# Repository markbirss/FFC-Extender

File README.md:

# FFC-Extender and Adapter
FFC (Flexible Flat Cable) Extender and Adapter.

* Open-Source and released under the [Creative Commons Attribution Share-Alike License](https://creativecommons.org/licenses/by-sa/4.0/).
* **[Documentation on learn.watterott.com](https://learn.watterott.com)**

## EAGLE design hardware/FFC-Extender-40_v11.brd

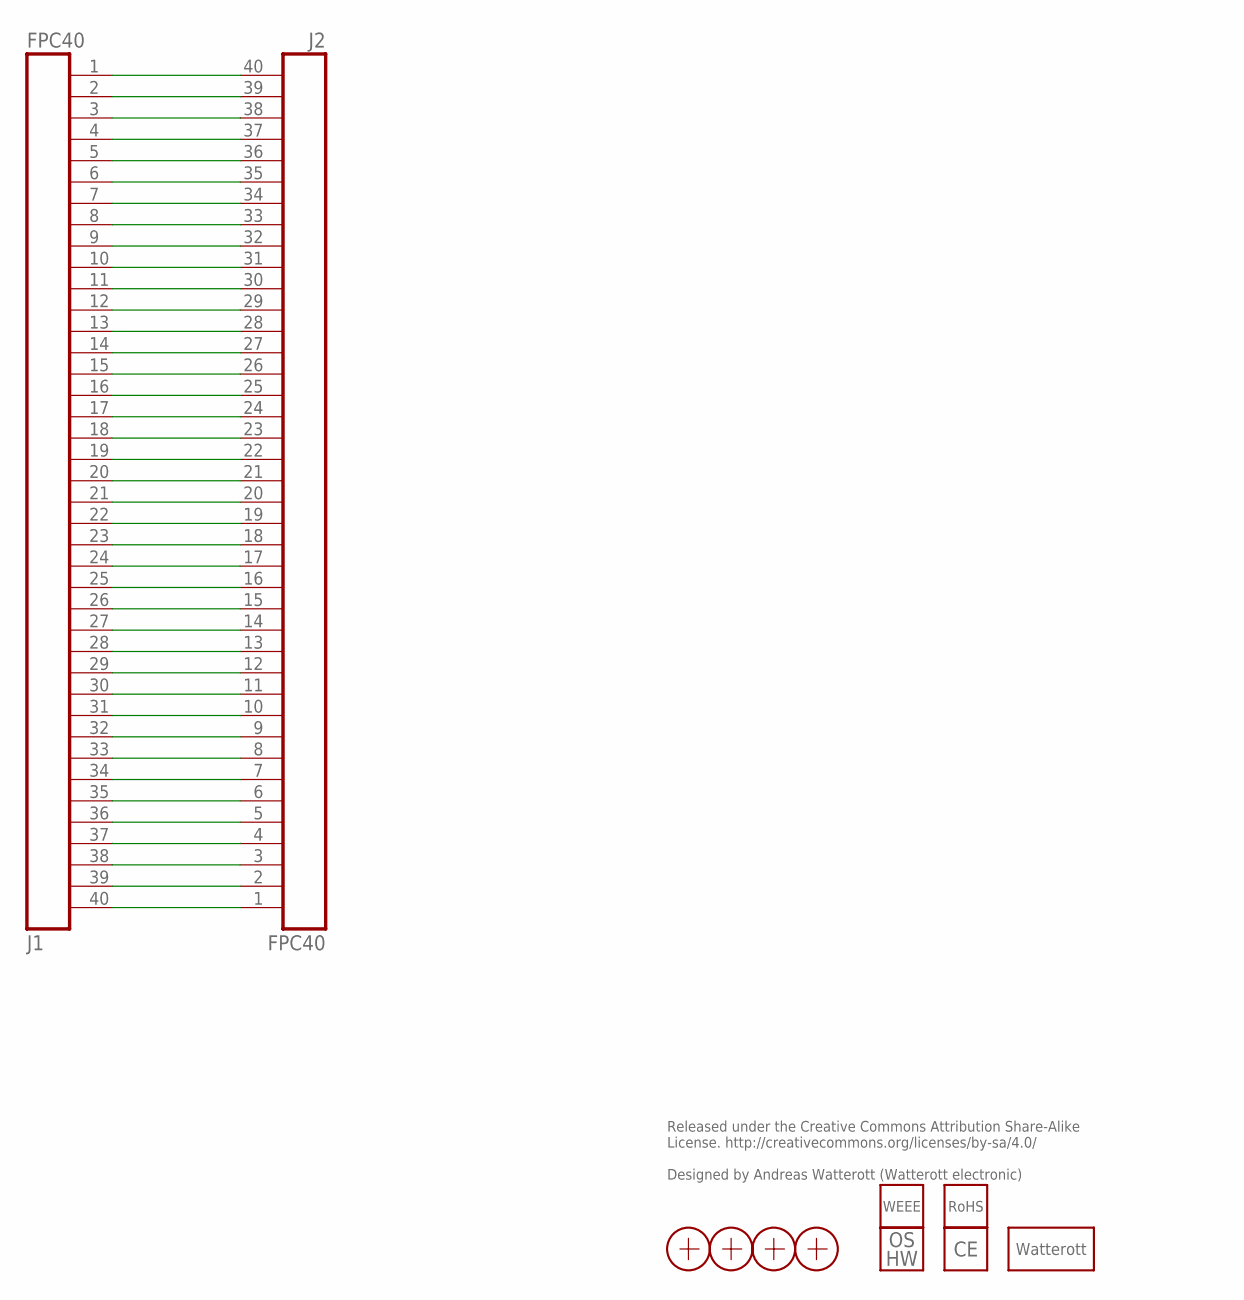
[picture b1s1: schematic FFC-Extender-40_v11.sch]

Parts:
J1, J2: FPC40; FPC40-0.5
LOGO1: LOGO_SPARK-2; SPARK_2MM
LOGO2: LOGO_CE-2; CE_2MM
LOGO3: LOGO_OSHW-2; OSHW_2MM
LOGO4: LOGO_ROHS-2; ROHS_2MM
LOGO5: LOGO_WEEE-4; WEEE_4MM
X1, X2, X3, X4: PASSER

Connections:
unnamed: J1.1, J2.40
unnamed: J1.2, J2.39
unnamed: J1.3, J2.38
unnamed: J1.4, J2.37
unnamed: J1.5, J2.36
unnamed: J1.6, J2.35
unnamed: J1.7, J2.34
unnamed: J1.8, J2.33
unnamed: J1.9, J2.32
unnamed: J1.10, J2.31
unnamed: J1.11, J2.30
unnamed: J1.12, J2.29
unnamed: J1.13, J2.28
unnamed: J1.14, J2.27
unnamed: J1.15, J2.26
unnamed: J1.16, J2.25
unnamed: J1.17, J2.24
unnamed: J1.18, J2.23
unnamed: J1.19, J2.22
unnamed: J1.20, J2.21
unnamed: J1.21, J2.20
unnamed: J1.22, J2.19
unnamed: J1.23, J2.18
unnamed: J1.24, J2.17
unnamed: J1.25, J2.16
unnamed: J1.26, J2.15
unnamed: J1.27, J2.14
unnamed: J1.28, J2.13
unnamed: J1.29, J2.12
unnamed: J1.30, J2.11
unnamed: J1.31, J2.10
unnamed: J1.32, J2.9
unnamed: J1.33, J2.8
unnamed: J1.34, J2.7
unnamed: J1.35, J2.6
unnamed: J1.36, J2.5
unnamed: J1.37, J2.4
unnamed: J1.38, J2.3
unnamed: J1.39, J2.2
unnamed: J1.40, J2.1

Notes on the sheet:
Released under the Creative Commons Attribution Share-Alike License. http://creativecommons.org/licenses/by-sa/4.0/ Designed by Andreas Watterott (Watterott electronic)

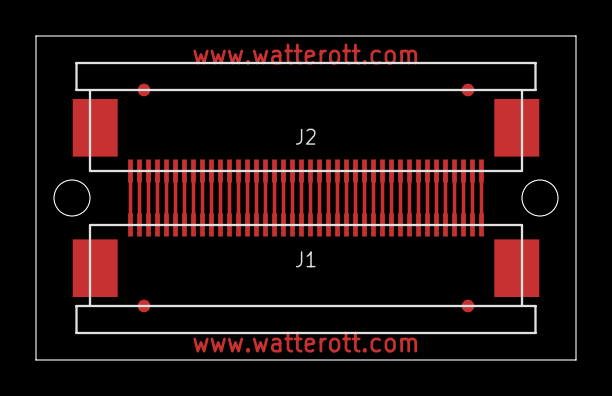
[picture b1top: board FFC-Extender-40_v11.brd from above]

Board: 2 copper layers, 30.0 x 18.0 mm, 11 parts (5 on the bottom side), 40 nets.

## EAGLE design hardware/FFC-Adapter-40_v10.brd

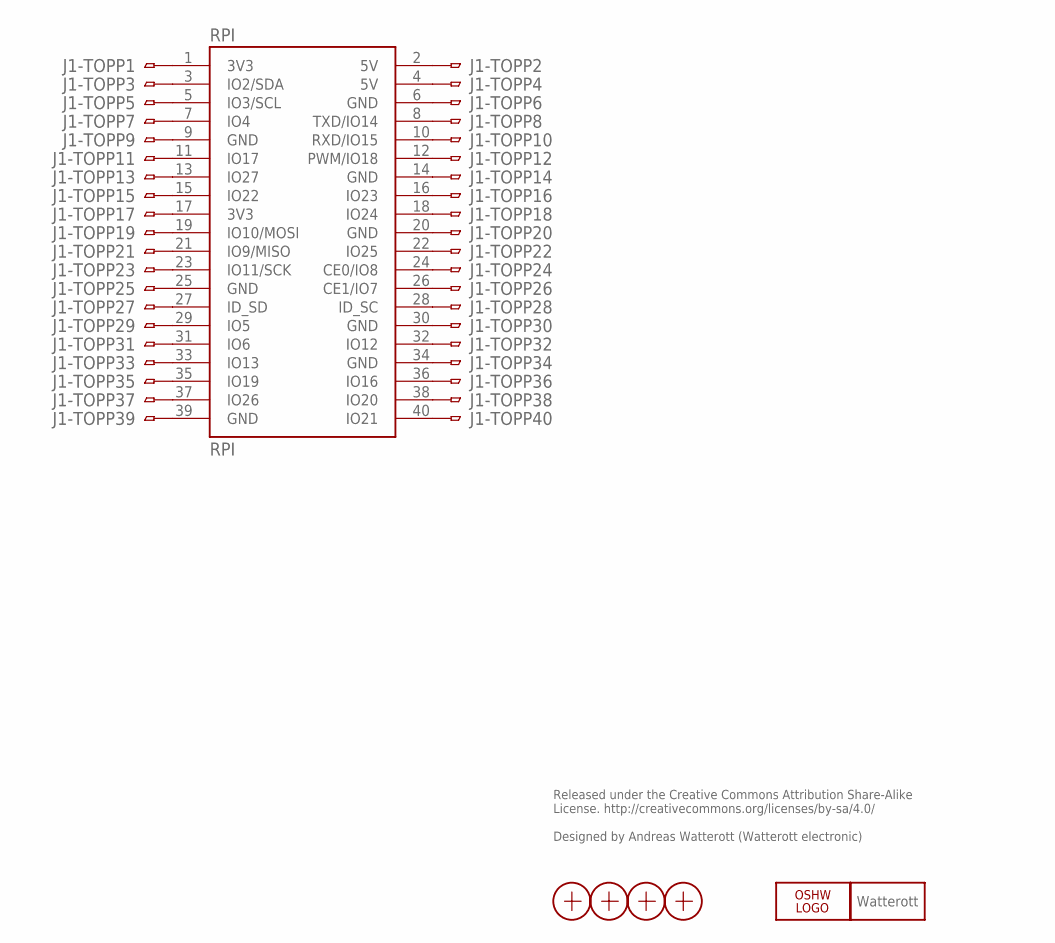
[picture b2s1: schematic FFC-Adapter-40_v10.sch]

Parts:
J1-TOP: FPC40_PIN; FPC40-0.5
LOGO1: OSHW_LOGO_6MILX0150-NT; OSHW_6X150_NOTEXT
LOGO3: LOGO_SPARK-4; SPARK_4MM
RPI: RPI; RPI-B+_CON
X1, X2, X3, X4: PASSER

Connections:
unnamed: J1-TOP.40, RPI.40 (IO21)
unnamed: J1-TOP.2, RPI.2 (5V)
unnamed: J1-TOP.3, RPI.3 (IO2/SDA)
unnamed: J1-TOP.4, RPI.4 (5V)
unnamed: J1-TOP.6, RPI.6 (GND)
unnamed: J1-TOP.5, RPI.5 (IO3/SCL)
unnamed: J1-TOP.7, RPI.7 (IO4)
unnamed: J1-TOP.8, RPI.8 (TXD/IO14)
unnamed: J1-TOP.9, RPI.9 (GND)
unnamed: J1-TOP.10, RPI.10 (RXD/IO15)
unnamed: J1-TOP.11, RPI.11 (IO17)
unnamed: J1-TOP.12, RPI.12 (PWM/IO18)
unnamed: J1-TOP.13, RPI.13 (IO27)
unnamed: J1-TOP.14, RPI.14 (GND)
unnamed: J1-TOP.15, RPI.15 (IO22)
unnamed: J1-TOP.16, RPI.16 (IO23)
unnamed: J1-TOP.17, RPI.17 (3V3)
unnamed: J1-TOP.18, RPI.18 (IO24)
unnamed: J1-TOP.19, RPI.19 (IO10/MOSI)
unnamed: J1-TOP.20, RPI.20 (GND)
unnamed: J1-TOP.21, RPI.21 (IO9/MISO)
unnamed: J1-TOP.22, RPI.22 (IO25)
unnamed: J1-TOP.23, RPI.23 (IO11/SCK)
unnamed: J1-TOP.24, RPI.24 (CE0/IO8)
unnamed: J1-TOP.25, RPI.25 (GND)
unnamed: J1-TOP.26, RPI.26 (CE1/IO7)
unnamed: J1-TOP.27, RPI.27 (ID_SD)
unnamed: J1-TOP.28, RPI.28 (ID_SC)
unnamed: J1-TOP.29, RPI.29 (IO5)
unnamed: J1-TOP.30, RPI.30 (GND)
unnamed: J1-TOP.31, RPI.31 (IO6)
unnamed: J1-TOP.32, RPI.32 (IO12)
unnamed: J1-TOP.33, RPI.33 (IO13)
unnamed: J1-TOP.34, RPI.34 (GND)
unnamed: J1-TOP.35, RPI.35 (IO19)
unnamed: J1-TOP.36, RPI.36 (IO16)
unnamed: J1-TOP.37, RPI.37 (IO26)
unnamed: J1-TOP.38, RPI.38 (IO20)
unnamed: J1-TOP.1, RPI.1 (3V3)
unnamed: J1-TOP.39, RPI.39 (GND)

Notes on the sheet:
Released under the Creative Commons Attribution Share-Alike License. http://creativecommons.org/licenses/by-sa/4.0/ Designed by Andreas Watterott (Watterott electronic)

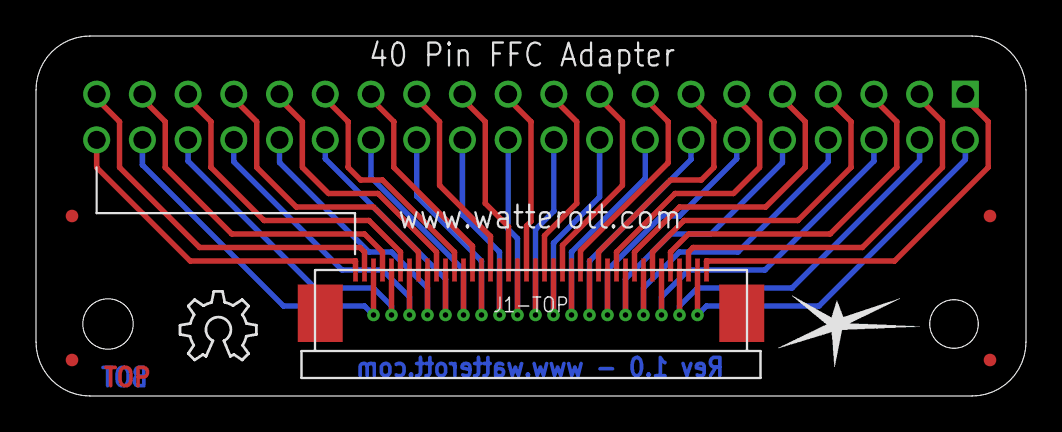
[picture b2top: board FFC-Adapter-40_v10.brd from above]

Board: 2 copper layers, 55.0 x 20.0 mm, 8 parts (0 on the bottom side), 40 nets.

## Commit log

2020-11-03 added rev 1.1
